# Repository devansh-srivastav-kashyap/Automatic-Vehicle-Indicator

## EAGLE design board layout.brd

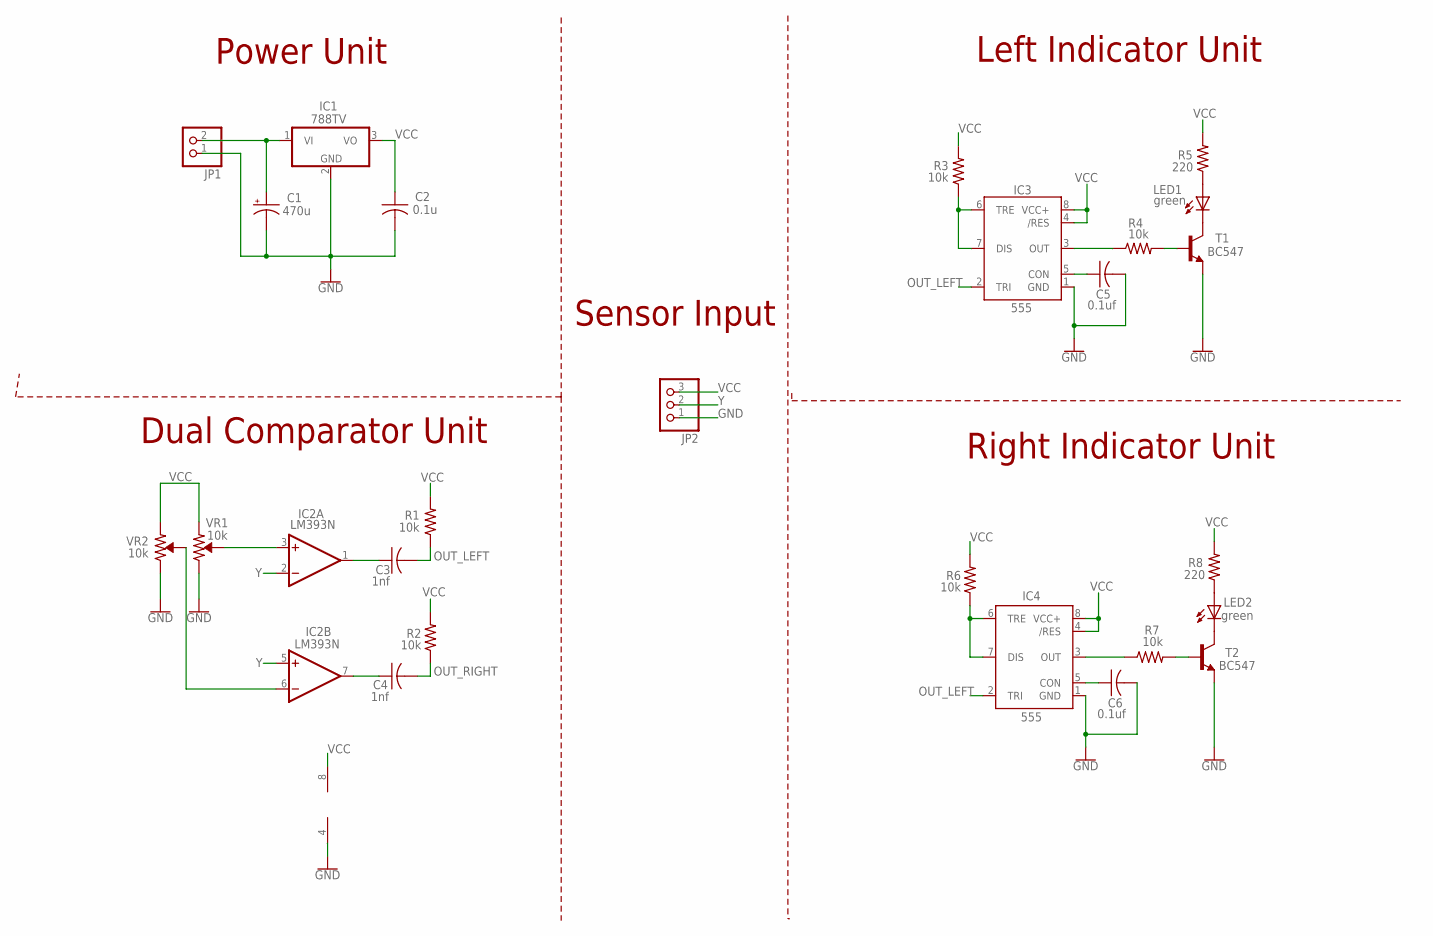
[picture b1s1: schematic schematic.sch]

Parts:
C1: 470u; E2-4
C2: 0.1u; C025-025X050
C3, C4: 1nf; C025-025X050
C5, C6: 0.1uf; C025-025X050
IC1: 788TV; TO220V
IC2: LM393N; DIL08
IC3, IC4: 555; DIP08-KIT
JP1: PINHD-1X2; 1X02
JP2: PINHD-1X3; 1X03
LED1, LED2: green; LED5MM
R1, R2, R3, R4, R6, R7: 10k; 0204/5
R5, R8: 220; 0204/5
T1, T2: BC547; TO92
VR1, VR2: 10k; TRIMPOT-PTH-3386U

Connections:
GND: C1.-, C2.2, C5.2, C6.2, IC1.2 (GND), IC2.4 (V-), IC3.1 (GND), IC4.1 (GND), JP1.1, JP2.1, T1.1 (E), T2.1 (E), VR1.3 (CW), VR2.3 (CW)
unnamed: C1.+, IC1.1 (VI), JP1.2
unnamed: IC2.3 (+IN), VR1.2 (WIPER)
unnamed: IC2.6 (-IN), VR2.2 (WIPER)
unnamed: C3.1, IC2.1 (OUT)
unnamed: C4.1, IC2.7 (OUT)
unnamed: C5.1, IC3.5 (CON)
unnamed: IC3.6 (TRE), IC3.7 (DIS), R3.1
unnamed: IC3.3 (OUT), R4.1
unnamed: R4.2, T1.2 (B)
unnamed: LED1.K (C), T1.3 (C)
unnamed: LED1.A, R5.1
unnamed: C6.1, IC4.5 (CON)
unnamed: IC4.6 (TRE), IC4.7 (DIS), R6.1
unnamed: IC4.3 (OUT), R7.1
unnamed: R7.2, T2.2 (B)
unnamed: LED2.K (C), T2.3 (C)
unnamed: LED2.A, R8.1
OUT_LEFT: C3.2, IC3.2 (TRI), IC4.2 (TRI), R1.1
OUT_RIGHT: C4.2, R2.1
VCC: C2.1, IC1.3 (VO), IC2.8 (V+), IC3.4 (/RES), IC3.8 (VCC+), IC4.4 (/RES), IC4.8 (VCC+), JP2.3, R1.2, R2.2, R3.2, R5.2, R6.2, R8.2, VR1.1 (CCW), VR2.1 (CCW)
Y: IC2.2 (-IN), IC2.5 (+IN), JP2.2

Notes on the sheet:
Power Unit
Left Indicator Unit
Right Indicator Unit
Dual Comparator Unit
Sensor Input

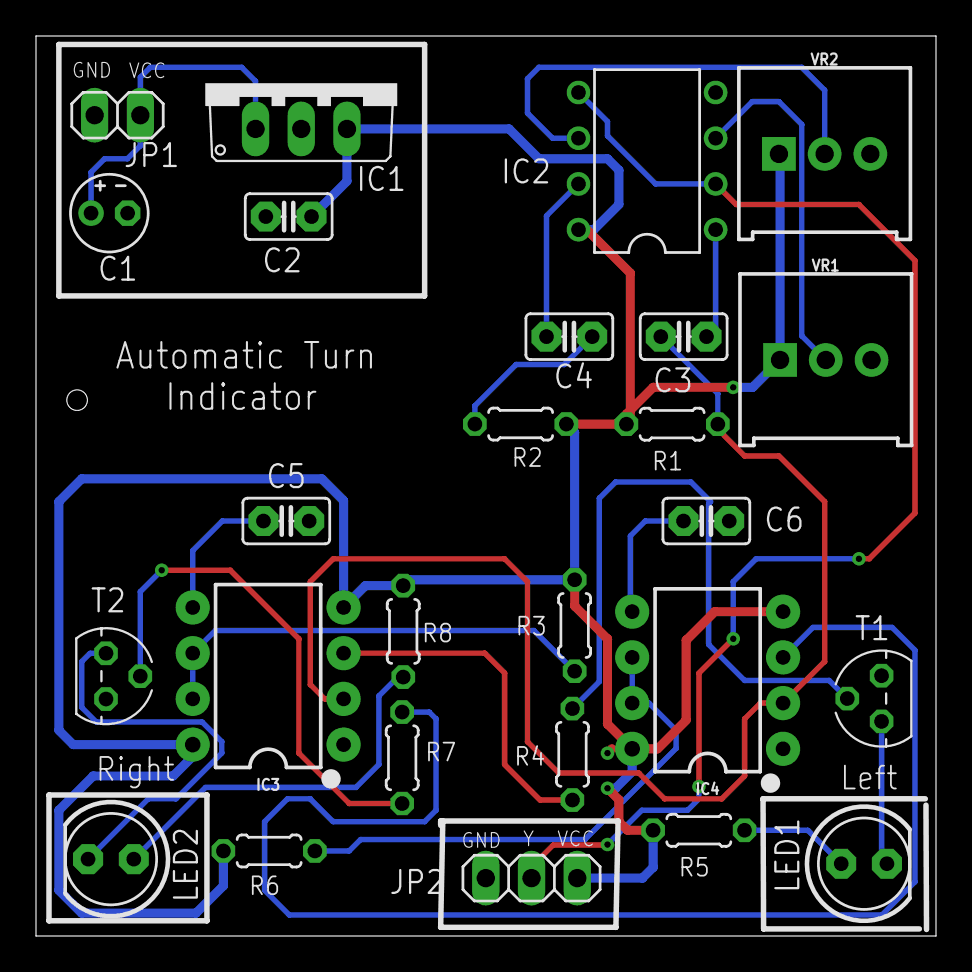
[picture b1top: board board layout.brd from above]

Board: 2 copper layers, 50.0 x 50.0 mm, 26 parts (0 on the bottom side), 22 nets.

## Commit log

2021-09-30 Designs on PDF

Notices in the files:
parts and their libraries:
SparkFun-IC-Special-Function: Licensing: Creative Commons ShareAlike 4.0 International - https://creativecommons.org/licenses/by-sa/4.0
